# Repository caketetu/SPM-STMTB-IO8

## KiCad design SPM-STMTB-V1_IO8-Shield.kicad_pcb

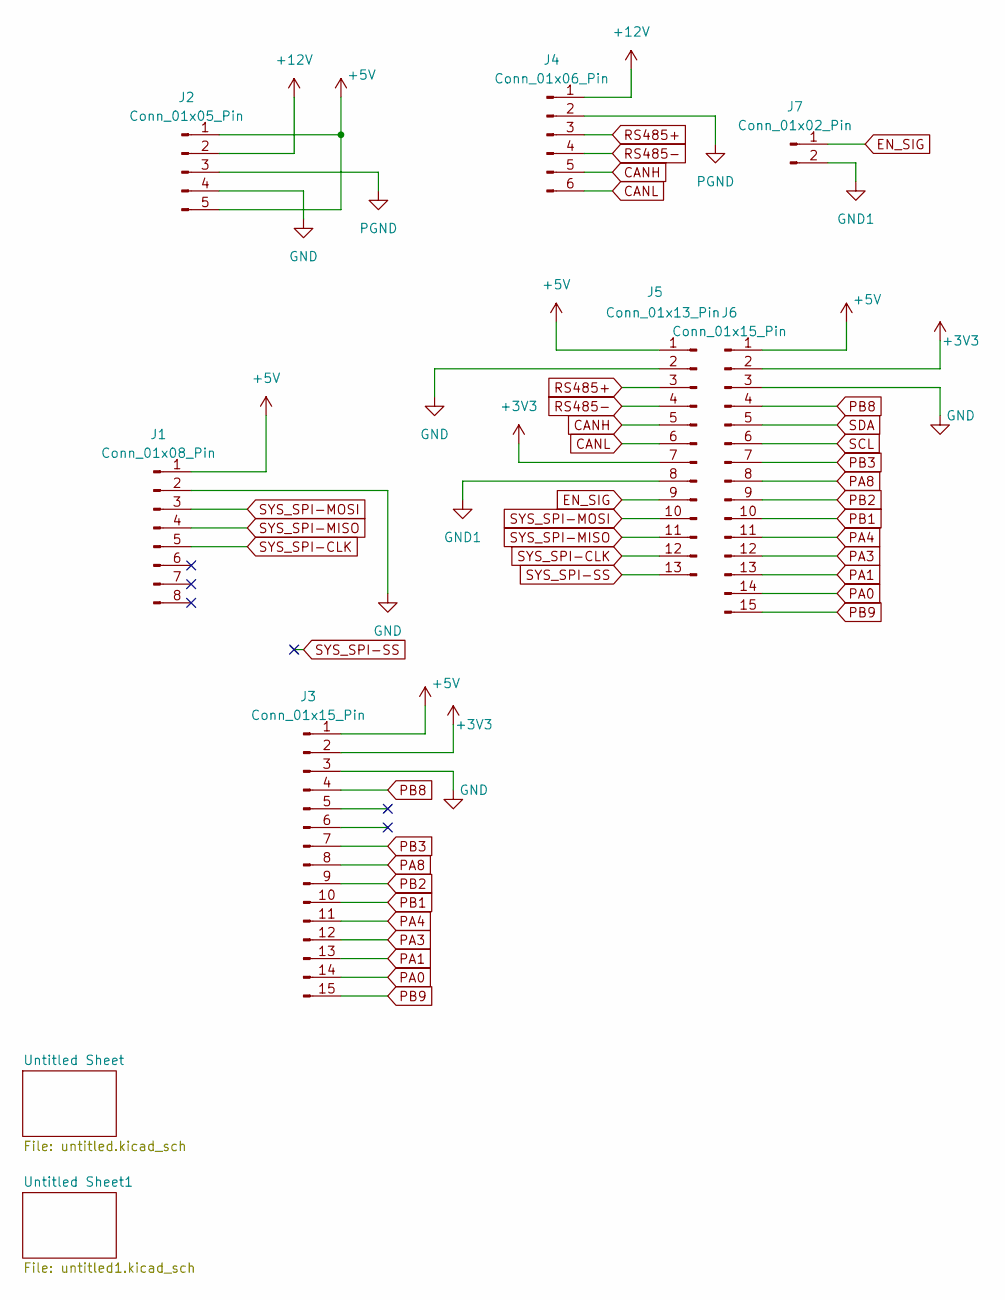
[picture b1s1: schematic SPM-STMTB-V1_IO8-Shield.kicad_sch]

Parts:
J1: Conn_01x08_Pin; PinSocket_1x08_P2.54mm_Vertical
J2: Conn_01x05_Pin; PinSocket_1x05_P2.54mm_Vertical
J3, J6: Conn_01x15_Pin; PinSocket_1x15_P2.54mm_Vertical
J4: Conn_01x06_Pin; PinHeader_1x06_P2.54mm_Vertical
J5: Conn_01x13_Pin; PinSocket_1x13_P2.54mm_Vertical
J7: Conn_01x02_Pin; PinSocket_1x02_P2.54mm_Vertical

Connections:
+3V3: J3.2, J5.7, J6.2
+5V: J1.1, J2.1, J2.5, J3.1, J5.1, J6.1; also elsewhere on the board
+12V: J2.2, J4.1
CANH: J4.5, J5.5
CANL: J4.6, J5.6
EN_SIG: J5.9, J7.1
GND: J1.2, J2.4, J3.3, J5.2, J6.3; also elsewhere on the board
GND1: J5.8, J7.2
PA0: J3.14, J6.14
PA1: J3.13, J6.13
PA3: J3.12, J6.12
PA4: J3.11, J6.11
PA8: J3.8, J6.8
PB1: J3.10, J6.10
PB2: J3.9, J6.9
PB3: J3.7, J6.7
PB8: J3.4, J6.4
PB9: J3.15, J6.15
PGND: J2.3, J4.2
RS485+: J4.3, J5.3
RS485-: J4.4, J5.4
SCL: J6.6; also elsewhere on the board
SDA: J6.5; also elsewhere on the board
SYS_SPI-CLK: J1.5, J5.12
SYS_SPI-MISO: J1.4, J5.11
SYS_SPI-MOSI: J1.3, J5.10
SYS_SPI-SS: J5.13

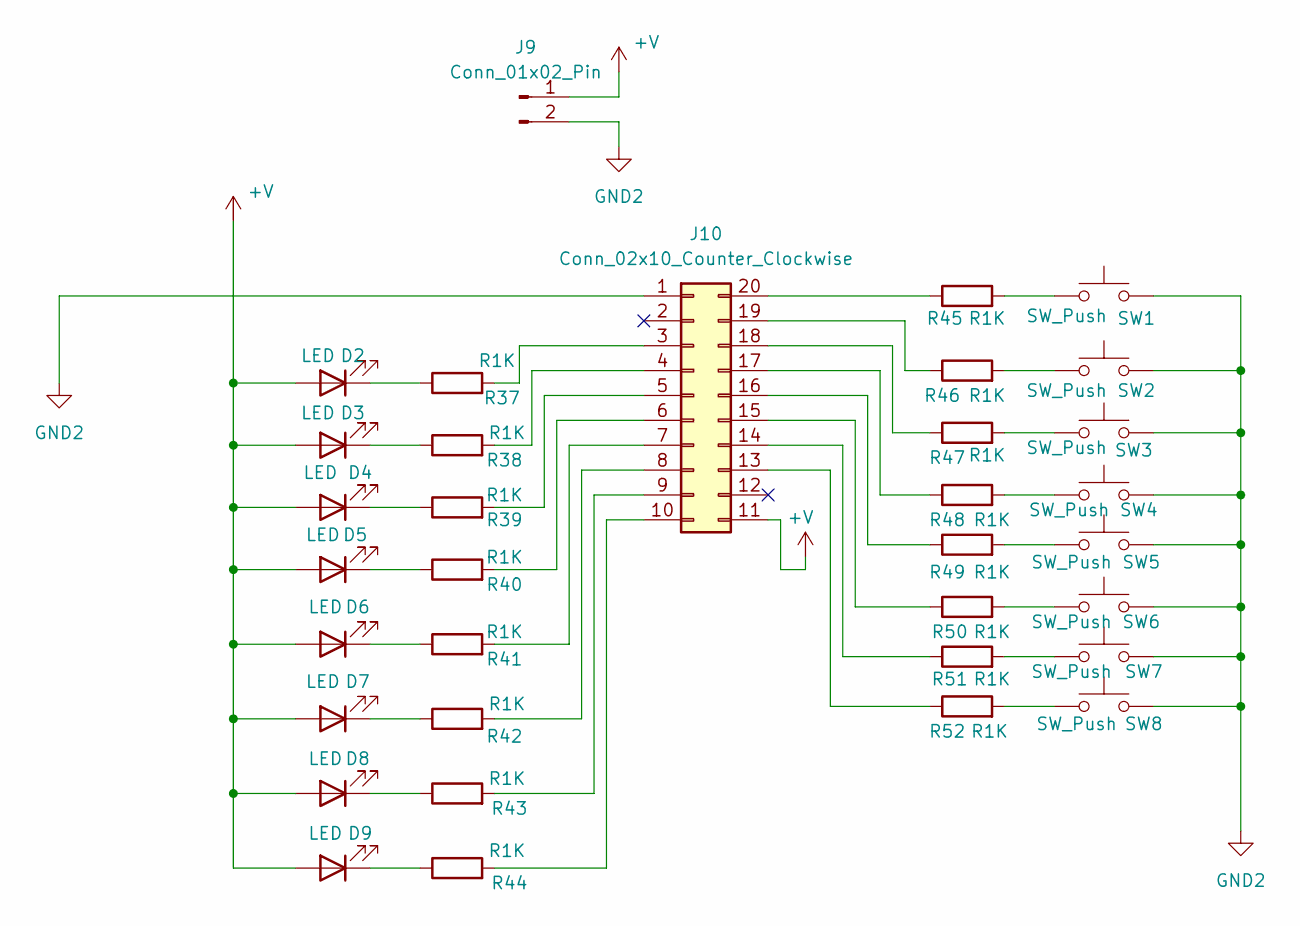
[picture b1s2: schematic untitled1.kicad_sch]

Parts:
D2, D3, D4, D5, D6, D7, D8, D9: LED; LED_0603_1608Metric
J9: Conn_01x02_Pin; PinHeader_1x02_P2.54mm_Vertical
J10: Conn_02x10_Counter_Clockwise; IDC-Header_2x10_P2.54mm_Vertical
R37, R38, R39, R40, R41, R42, R43, R44, R45, R46, R47, R48, R49, R50, R51, R52: R1K; R_0603_1608Metric
SW1, SW2, SW3, SW4, SW5, SW6, SW7, SW8: SW_Push; SW_PUSH_6mm

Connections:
+V: D2.2 (A), D3.2 (A), D4.2 (A), D5.2 (A), D6.2 (A), D7.2 (A), D8.2 (A), D9.2 (A), J9.1, J10.11
GND2: J9.2, J10.1, SW1.2, SW2.2, SW3.2, SW4.2, SW5.2, SW6.2, SW7.2, SW8.2
unnamed: D2.1 (K), R37.1
unnamed: D3.1 (K), R38.1
unnamed: D4.1 (K), R39.1
unnamed: D5.1 (K), R40.1
unnamed: D6.1 (K), R41.1
unnamed: D7.1 (K), R42.1
unnamed: D8.1 (K), R43.1
unnamed: D9.1 (K), R44.1
unnamed: J10.3, R37.2
unnamed: J10.4, R38.2
unnamed: J10.5, R39.2
unnamed: J10.6, R40.2
unnamed: J10.7, R41.2
unnamed: J10.8, R42.2
unnamed: J10.9, R43.2
unnamed: J10.10, R44.2
unnamed: J10.13, R52.1
unnamed: J10.14, R51.1
unnamed: J10.15, R50.1
unnamed: J10.16, R49.1
unnamed: J10.17, R48.1
unnamed: J10.18, R47.1
unnamed: J10.19, R46.1
unnamed: J10.20, R45.1
unnamed: R45.2, SW1.1
unnamed: R46.2, SW2.1
unnamed: R47.2, SW3.1
unnamed: R48.2, SW4.1
unnamed: R49.2, SW5.1
unnamed: R50.2, SW6.1
unnamed: R51.2, SW7.1
unnamed: R52.2, SW8.1

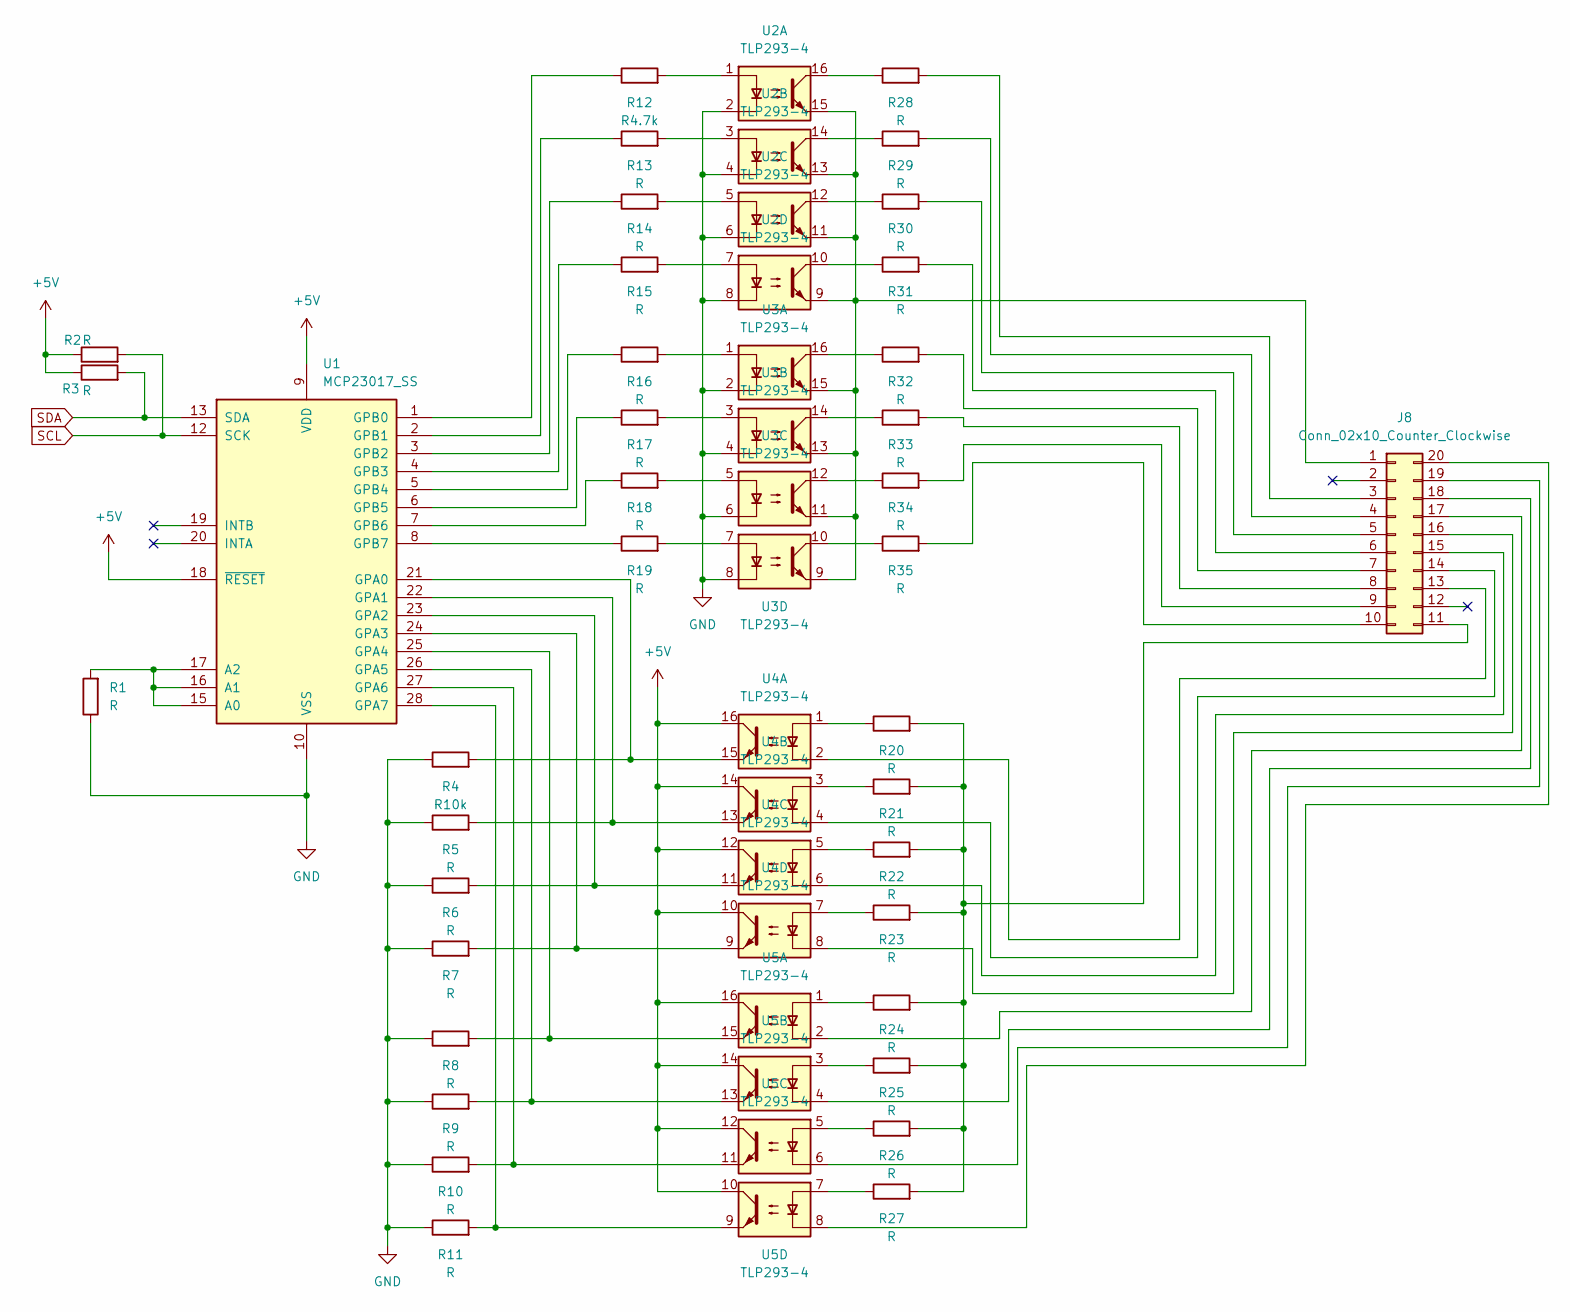
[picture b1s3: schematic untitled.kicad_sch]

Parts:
J8: Conn_02x10_Counter_Clockwise; IDC-Header_2x10_P2.54mm_Vertical
R1, R2, R3, R5, R6, R7, R8, R9, R10, R11, R13, R14, R15, R16, R17, R18, R19, R20, R21, R22, R23, R24, R25, R26, R27, R28, R29, R30, R31, R32, R33, R34, R35: R; R_0603_1608Metric
R4: R10k; R_0603_1608Metric
R12: R4.7k; R_0603_1608Metric
U1: MCP23017_SS; SSOP-28_5.3x10.2mm_P0.65mm
U2, U3, U4, U5: TLP293-4; SOIC-16_4.55x10.3mm_P1.27mm

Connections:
+5V: R2.1, R3.1, U1.9 (VDD), U1.18 (~RESET), U4.10, U4.12, U4.14, U4.16, U5.10, U5.12, U5.14, U5.16; also elsewhere on the board
GND: R1.1, R4.1, R5.1, R6.1, R7.1, R8.1, R9.1, R10.1, R11.1, U1.10 (VSS), U2.2, U2.4, U2.6, U2.8, U3.2, U3.4, U3.6, U3.8; also elsewhere on the board
unnamed: J8.1, U2.9, U2.11, U2.13, U2.15, U3.9, U3.11, U3.13, U3.15
unnamed: J8.3, R28.2
unnamed: J8.4, R29.2
unnamed: J8.5, R30.2
unnamed: J8.6, R31.2
unnamed: J8.7, R32.2
unnamed: J8.8, R33.2
unnamed: J8.9, R34.2
unnamed: J8.10, R35.2
unnamed: J8.11, R20.2, R21.2, R22.2, R23.2, R24.2, R25.2, R26.2, R27.2
unnamed: J8.13, U4.2
unnamed: J8.14, U4.4
unnamed: J8.15, U4.6
unnamed: J8.16, U4.8
unnamed: J8.17, U5.2
unnamed: J8.18, U5.4
unnamed: J8.19, U5.6
unnamed: J8.20, U5.8
unnamed: R12.2, U2.1
unnamed: R13.2, U2.3
unnamed: R14.2, U2.5
unnamed: R15.2, U2.7
unnamed: R16.2, U3.1
unnamed: R17.2, U3.3
unnamed: R18.2, U3.5
unnamed: R19.2, U3.7
unnamed: R20.1, U4.1
unnamed: R21.1, U4.3
unnamed: R22.1, U4.5
unnamed: R23.1, U4.7
unnamed: R24.1, U5.1
unnamed: R25.1, U5.3
unnamed: R26.1, U5.5
unnamed: R27.1, U5.7
unnamed: R28.1, U2.16
unnamed: R29.1, U2.14
unnamed: R30.1, U2.12
unnamed: R31.1, U2.10
unnamed: R32.1, U3.16
unnamed: R33.1, U3.14
unnamed: R34.1, U3.12
unnamed: R35.1, U3.10
unnamed: R1.2, U1.15 (A0), U1.16 (A1), U1.17 (A2)
unnamed: R4.2, U1.21 (GPA0), U4.15
unnamed: R5.2, U1.22 (GPA1), U4.13
unnamed: R6.2, U1.23 (GPA2), U4.11
unnamed: R7.2, U1.24 (GPA3), U4.9
unnamed: R8.2, U1.25 (GPA4), U5.15
unnamed: R9.2, U1.26 (GPA5), U5.13
unnamed: R10.2, U1.27 (GPA6), U5.11
unnamed: R11.2, U1.28 (GPA7), U5.9
unnamed: R12.1, U1.1 (GPB0)
unnamed: R13.1, U1.2 (GPB1)
unnamed: R14.1, U1.3 (GPB2)
unnamed: R15.1, U1.4 (GPB3)
unnamed: R16.1, U1.5 (GPB4)
unnamed: R17.1, U1.6 (GPB5)
unnamed: R18.1, U1.7 (GPB6)
unnamed: R19.1, U1.8 (GPB7)
SCL: R2.2, U1.12 (SCK); also elsewhere on the board
SDA: R3.2, U1.13 (SDA); also elsewhere on the board

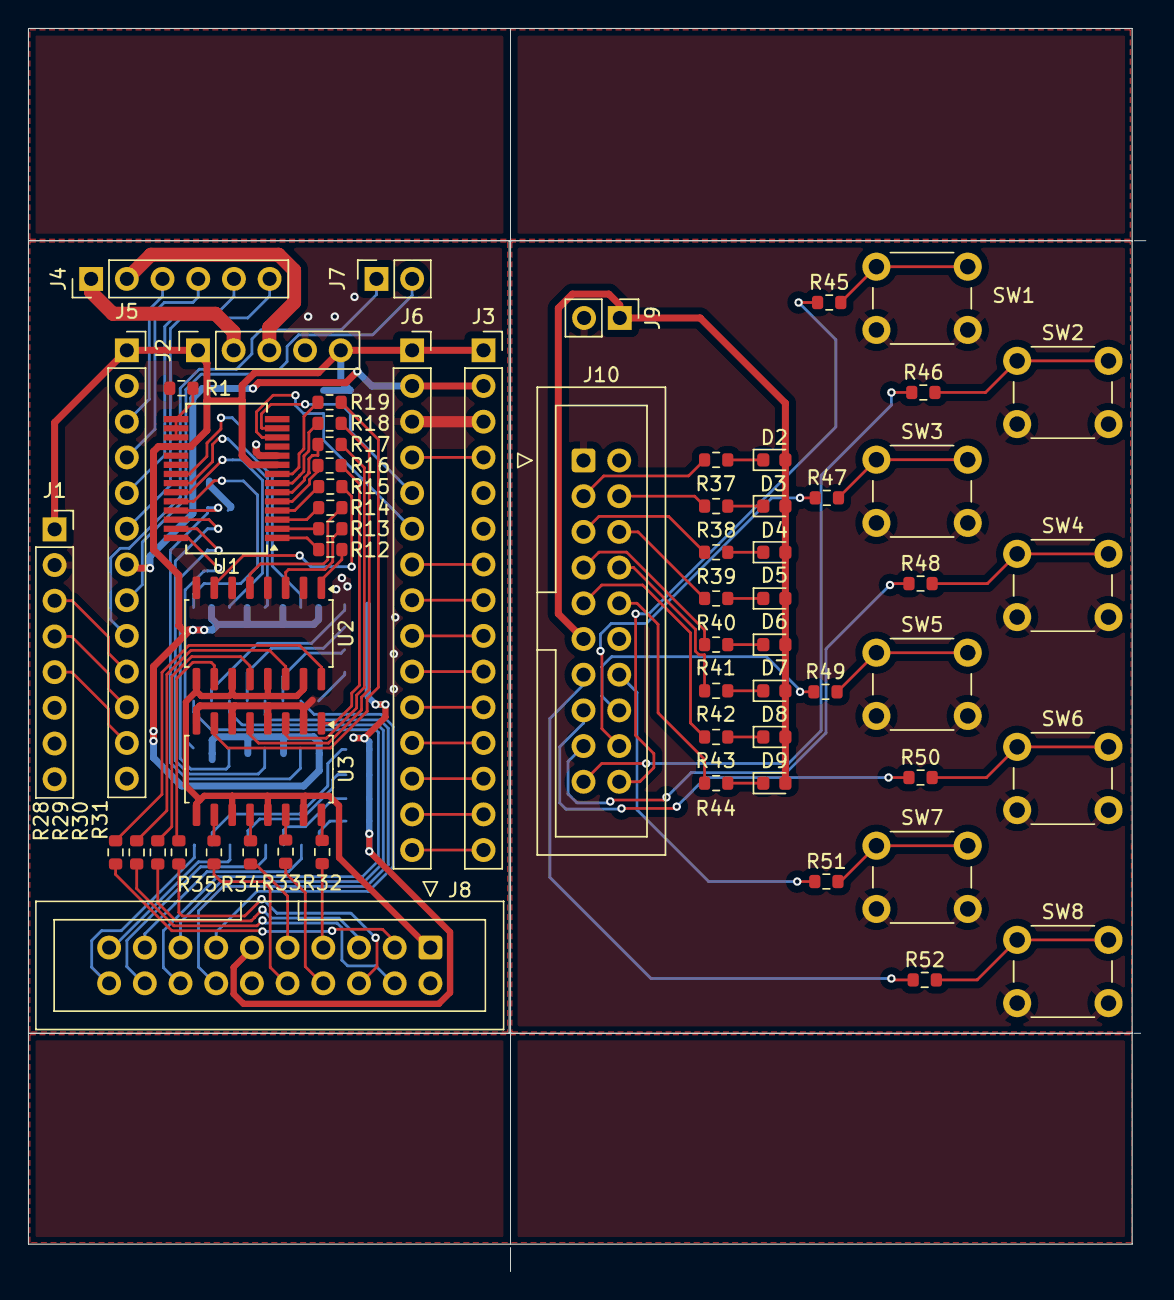
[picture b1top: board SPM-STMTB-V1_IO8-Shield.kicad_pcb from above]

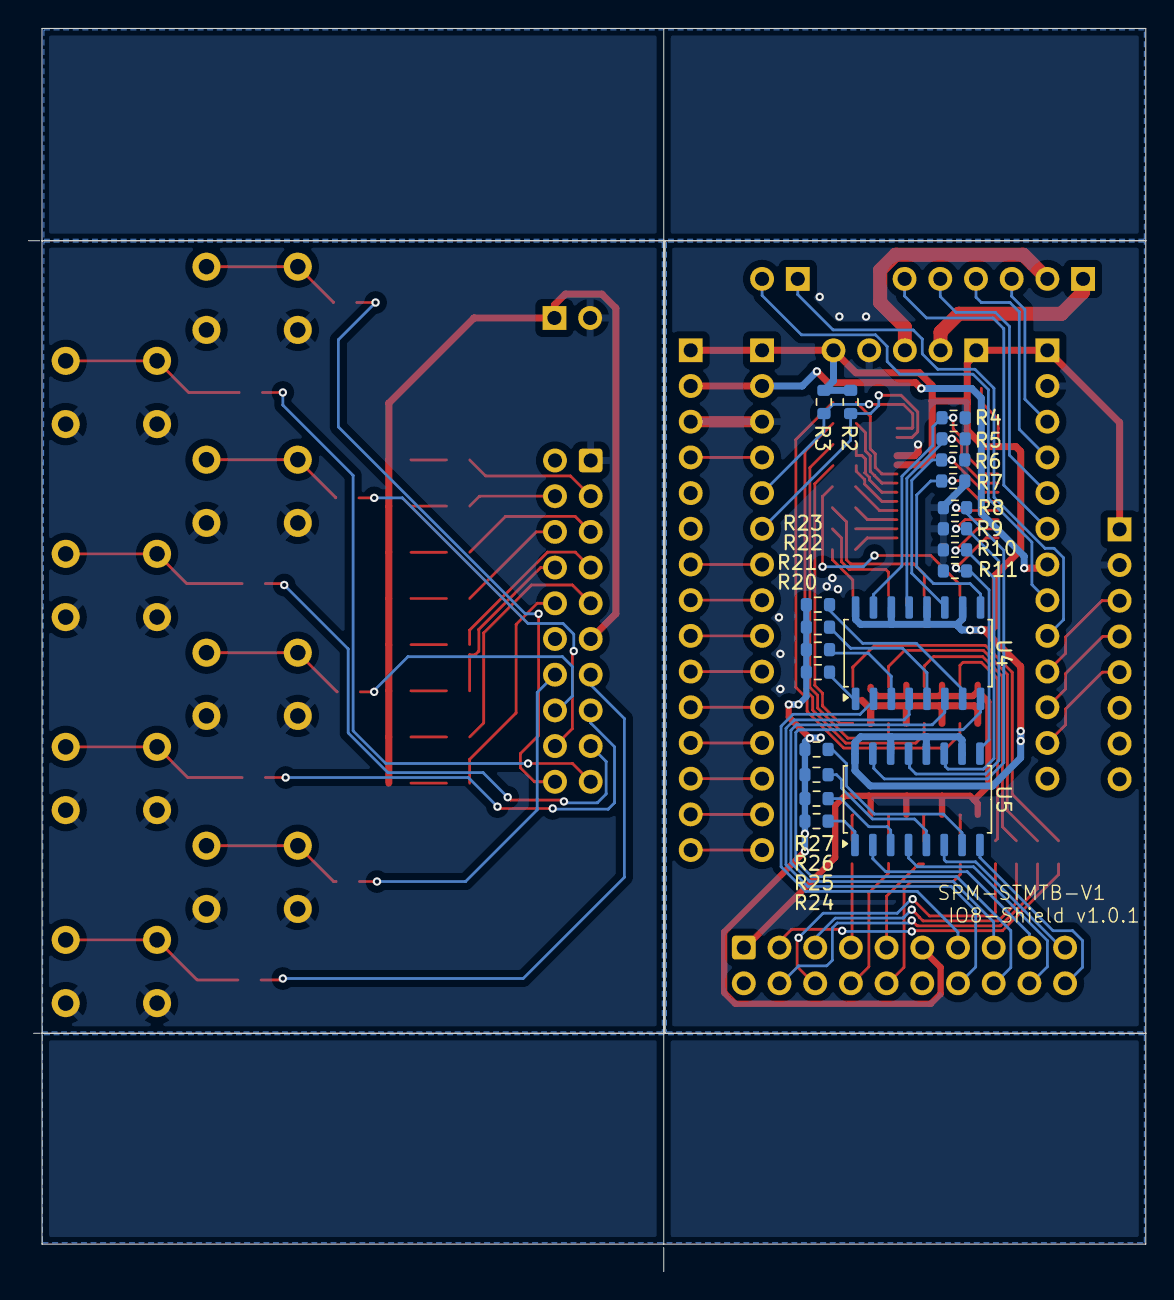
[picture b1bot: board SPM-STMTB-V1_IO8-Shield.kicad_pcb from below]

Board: 2 copper layers, 79.5 x 88.4 mm, 82 parts (20 on the bottom side), 119 nets.
